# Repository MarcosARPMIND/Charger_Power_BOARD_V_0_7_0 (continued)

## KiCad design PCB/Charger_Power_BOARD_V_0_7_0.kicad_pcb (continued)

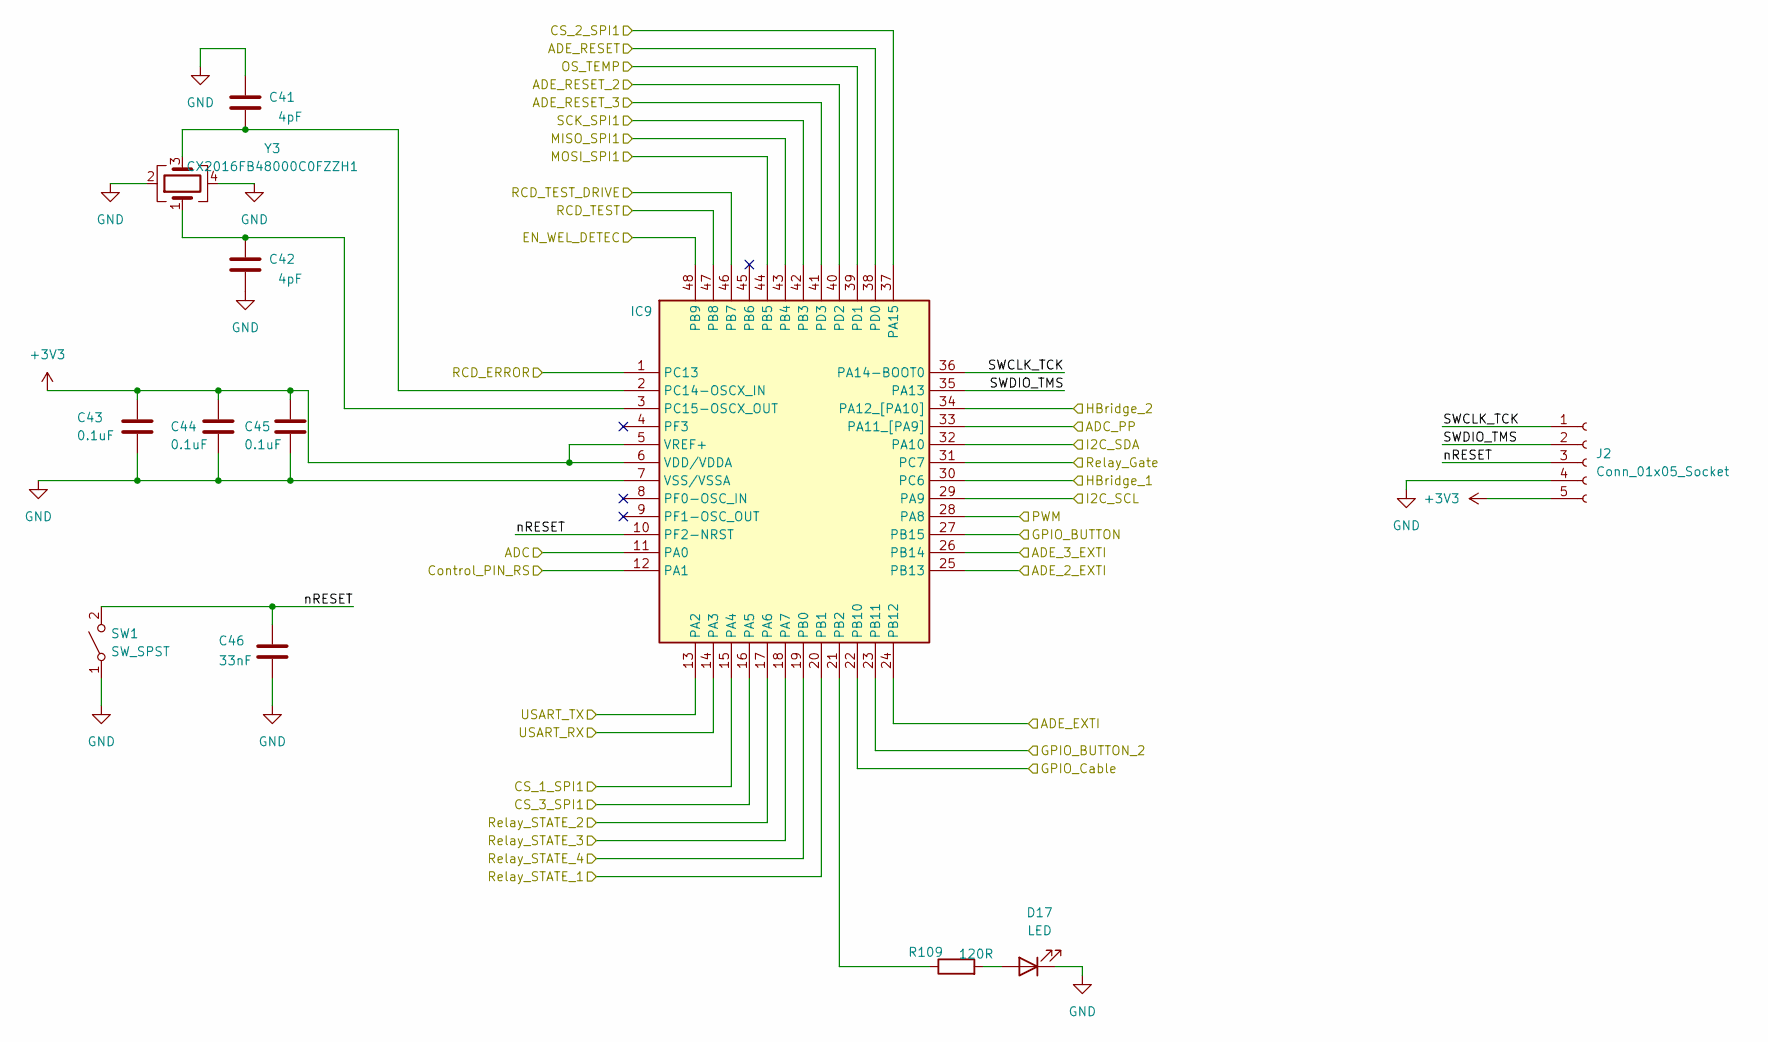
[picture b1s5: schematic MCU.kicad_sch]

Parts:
C41, C42: 4pF; C_0603_1608Metric_Pad1.08x0.95mm_HandSolder; MPN CC0603BRNPO9BN4R0
C43, C44, C45: 0.1uF; C_0603_1608Metric; MPN CL10B104MB8NNNC
C46: 33nF; C_0603_1608Metric_Pad1.08x0.95mm_HandSolder; MPN 0603B333J500CT
D17: LED; LED_0603_1608Metric
IC9: STM32C031C6T6; QFP50P900X900X160-48N; MPN STM32C031C6T6
J2: Conn_01x05_Socket; PinHeader_1x05_P2.54mm_Vertical
R109: 120R; R_0603_1608Metric; MPN RE0603FRE07150RL
SW1: SW_SPST; SW_SPST_B3U-1000P; MPN B3U-1000PM
Y3: CX2016FB48000C0FZZH1; Crystal_SMD_2016-4Pin_2.0x1.6mm; MPN CX2016FB48000C0FZZH1

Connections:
+3V3: C43.1, C44.1, C45.1, IC9.5 (VREF+), IC9.6 (VDD/VDDA), J2.5; also elsewhere on the board
/ADC_PP_resistor: IC9.33 (PA11_[PA9]); also elsewhere on the board
/ADE_RESET: IC9.38 (PD0); also elsewhere on the board
/ADE_RESET_2: IC9.40 (PD2); also elsewhere on the board
/ADE_RESET_3: IC9.41 (PD3); also elsewhere on the board
/CABLE_lock: IC9.22 (PB10); also elsewhere on the board
/Control_Pilot/Pilot_ADC: IC9.11 (PA0); also elsewhere on the board
/Control_Pilot/Pilot_PWM: IC9.28 (PA8); also elsewhere on the board
/EN_WEL_Detec: IC9.48 (PB9); also elsewhere on the board
/GPIO_BUTTON: IC9.27 (PB15); also elsewhere on the board
/GPIO_BUTTON_2: IC9.23 (PB11); also elsewhere on the board
/Gate_Relay: IC9.31 (PC7); also elsewhere on the board
/HBridge_1: IC9.30 (PC6); also elsewhere on the board
/HBridge_2: IC9.34 (PA12_[PA10]); also elsewhere on the board
/I2C_SCL: IC9.29 (PA9); also elsewhere on the board
/I2C_SDA: IC9.32 (PA10); also elsewhere on the board
/IRQ_ADE: IC9.24 (PB12); also elsewhere on the board
/IRQ_ADE_2: IC9.25 (PB13); also elsewhere on the board
/IRQ_ADE_3: IC9.26 (PB14); also elsewhere on the board
/Line_1_Status: IC9.20 (PB1); also elsewhere on the board
/Line_2_Status: IC9.17 (PA6); also elsewhere on the board
/Line_3_Status: IC9.18 (PA7); also elsewhere on the board
/MCU/SWCLK_TCK: IC9.36 (PA14-BOOT0), J2.1
/MCU/SWDIO_TMS: IC9.35 (PA13), J2.2
/MCU/nRESET: C46.2, IC9.10 (PF2-NRST), J2.3, SW1.2 (B)
/Neutral_Line_Status: IC9.19 (PB0); also elsewhere on the board
/OS_TEMP: IC9.39 (PD1); also elsewhere on the board
/RCD_FAULT: IC9.1 (PC13); also elsewhere on the board
/RCD_TEST_DRIVE: IC9.46 (PB7); also elsewhere on the board
/RDC_TEST: IC9.47 (PB8); also elsewhere on the board
/RS_CTRL_PIN: IC9.12 (PA1); also elsewhere on the board
/SPI_CS_1: IC9.15 (PA4); also elsewhere on the board
/SPI_CS_2: IC9.37 (PA15); also elsewhere on the board
/SPI_CS_3: IC9.16 (PA5); also elsewhere on the board
/SPI_MISO: IC9.43 (PB4); also elsewhere on the board
/SPI_MOSI: IC9.44 (PB5); also elsewhere on the board
/SPI_SCK: IC9.42 (PB3); also elsewhere on the board
/UART0_RX: IC9.14 (PA3); also elsewhere on the board
/UART0_TX: IC9.13 (PA2); also elsewhere on the board
GND: C41.2, C42.1, C43.2, C44.2, C45.2, C46.1, D17.1 (K), IC9.7 (VSS/VSSA), J2.4, SW1.1 (A), Y3.2, Y3.4; also elsewhere on the board
unnamed: D17.2 (A), R109.2
unnamed: IC9.21 (PB2), R109.1
unnamed: C41.1, IC9.2 (PC14-OSCX_IN), Y3.3
unnamed: C42.2, IC9.3 (PC15-OSCX_OUT), Y3.1

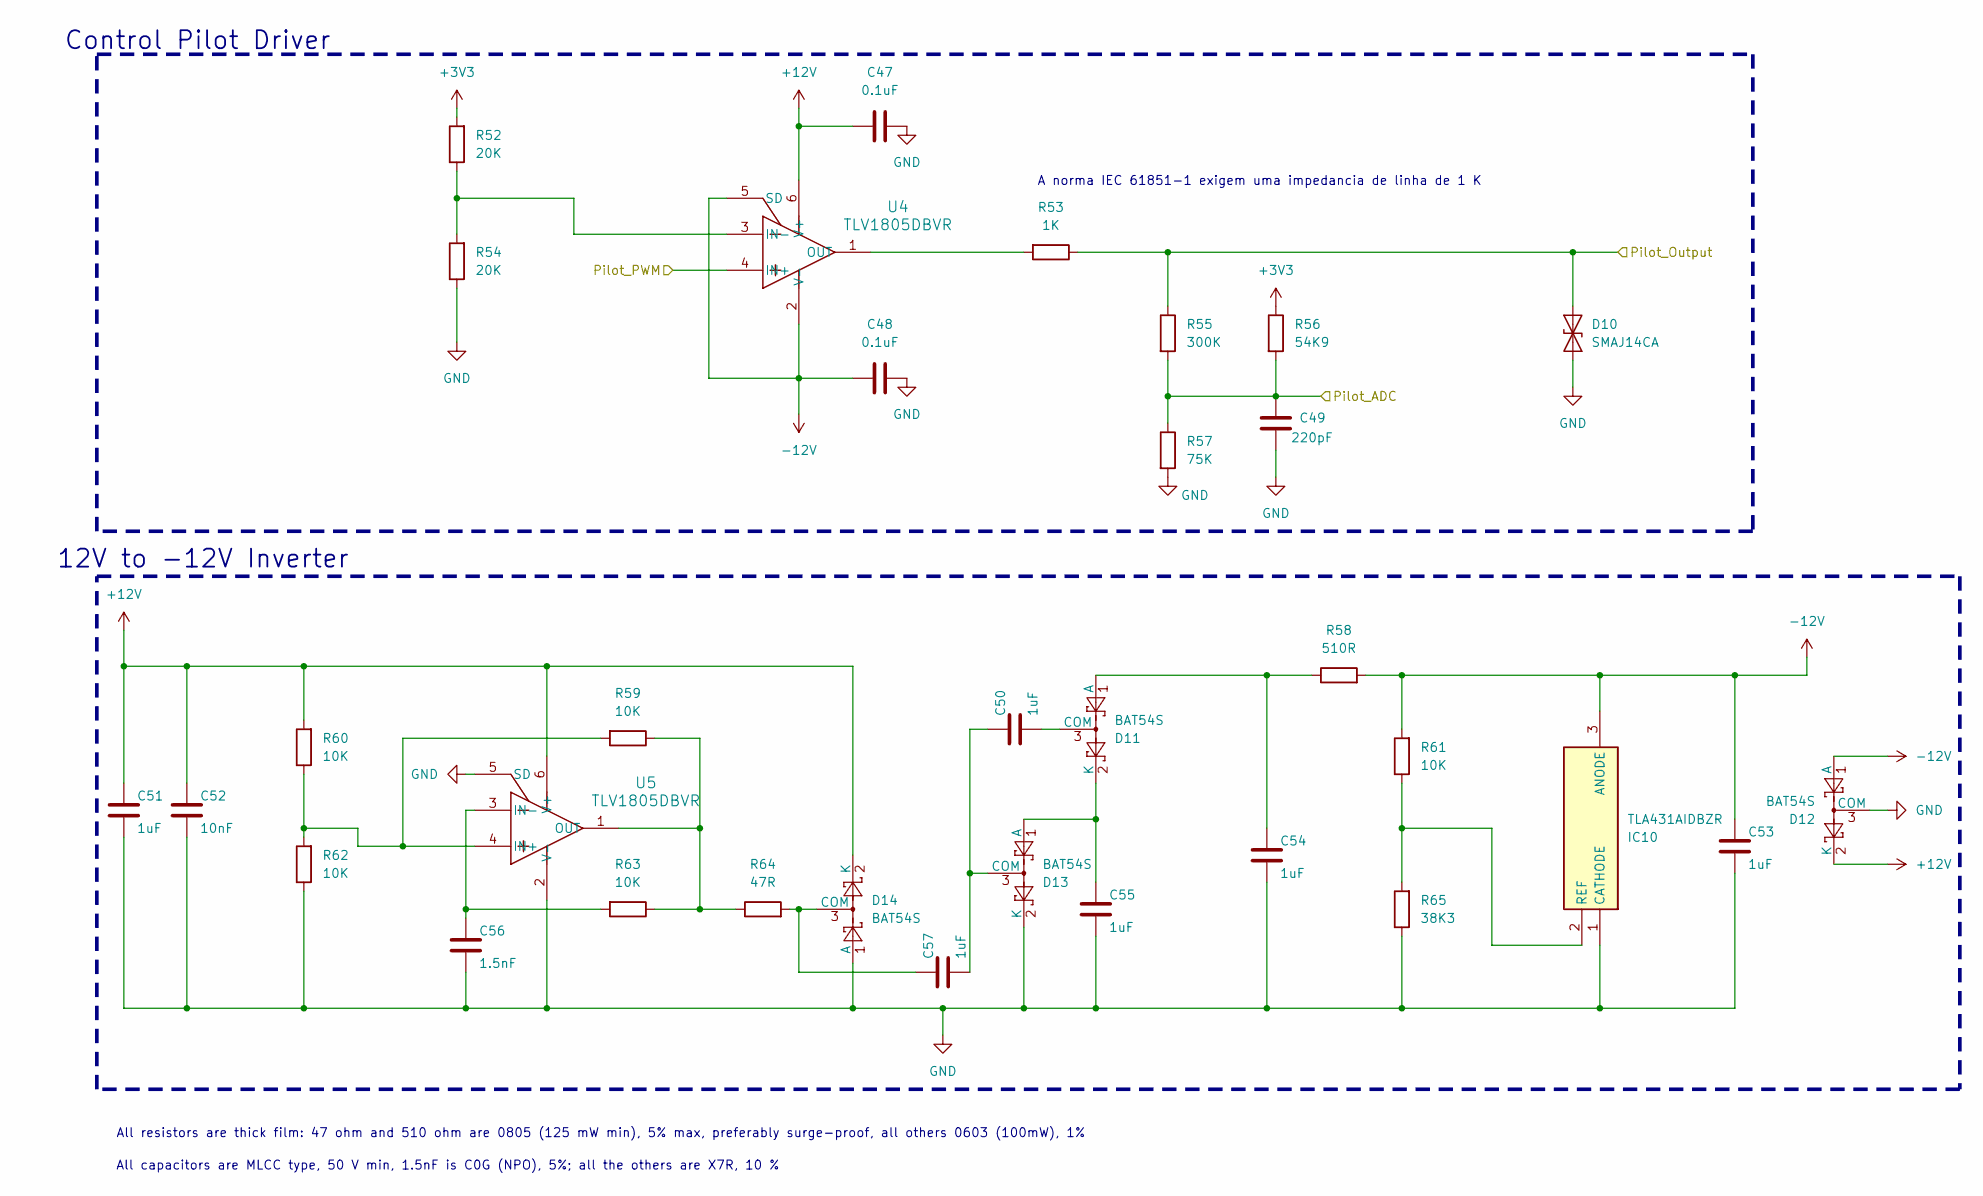
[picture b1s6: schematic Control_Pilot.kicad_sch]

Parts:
C47, C48: 0.1uF; C_0603_1608Metric; MPN CL10B104MB8NNNC
C49: 220pF; C_0603_1608Metric_Pad1.08x0.95mm_HandSolder; MPN CC0603JRX7R9BB221
C50, C51, C53, C54, C55, C57: 1uF; C_0603_1608Metric_Pad1.08x0.95mm_HandSolder; MPN CL10B105KB8NQNC
C52: 10nF; C_0603_1608Metric_Pad1.08x0.95mm_HandSolder; MPN 06035C103MAZ2A
C56: 1.5nF; C_0603_1608Metric_Pad1.08x0.95mm_HandSolder; MPN GCM1885C1H152JA16J
D10: SMAJ14CA; D_SMA; MPN SMAJ14CA-E3/61
D11, D12, D13, D14: BAT54S; SOT-23; MPN BAT54S-7-F
IC10: TLA431AIDBZR; SOT95P237X112-3N
R52, R54: 20K; R_0603_1608Metric; MPN CRCW060320K0FKEC
R53: 1K; R_1206_3216Metric; MPN CMP1206-FX-1001ELF
R55: 300K; R_0603_1608Metric
R56: 54K9; R_0603_1608Metric; MPN CRCW060354K9FKEA
R57: 75K; R_0603_1608Metric; MPN ERJ-PA3F7502V
R58: 510R; R_0805_2012Metric
R59, R60, R61, R62, R63: 10K; R_0603_1608Metric; MPN RCS060310K0FKEA
R64: 47R; R_0805_2012Metric; MPN CRCW080547R0JNEAC
R65: 38K3; R_0603_1608Metric; MPN CRCW060338K3FKEA
U4, U5: TLV1805DBVR; SOT95P280X145-6N; MPN TLV1805DBVR

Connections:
+3V3: R52.2, R56.1; also elsewhere on the board
+12V: C47.1, C51.1, C52.1, D12.2 (K), D14.2 (K), R60.2, U4.6 (V+), U5.6 (V+); also elsewhere on the board
-12V: C48.1, C53.1, D12.1 (A), IC10.3 (ANODE), R58.2, R61.2, U4.2 (V-), U4.5 (SD)
/Control_Pilot/Pilot_ADC: C49.2, R55.2, R56.2, R57.1; also elsewhere on the board
/Control_Pilot/Pilot_PWM: U4.4 (IN+); also elsewhere on the board
/PILOT_OUTPUT_CON: D10.1 (A1), R53.1, R55.1; also elsewhere on the board
GND: C47.2, C48.2, C49.1, C51.2, C52.2, C53.2, C54.2, C55.2, C56.2, D10.2 (A2), D12.3 (COM), D13.2 (K), D14.1 (A), IC10.1 (CATHODE), R54.1, R57.2, R62.1, R65.1, U5.2 (V-), U5.5 (SD); also elsewhere on the board
unnamed: C54.1, D11.1 (A), R58.1
unnamed: C50.2, D11.3 (COM)
unnamed: C55.1, D11.2 (K), D13.1 (A)
unnamed: C50.1, C57.2, D13.3 (COM)
unnamed: C57.1, D14.3 (COM), R64.2
unnamed: IC10.2 (REF), R61.1, R65.2
unnamed: R52.1, R54.2, U4.3 (IN-)
unnamed: R53.2, U4.1 (OUT)
unnamed: R59.2, R60.1, R62.2, U5.4 (IN+)
unnamed: C56.1, R63.2, U5.3 (IN-)
unnamed: R59.1, R63.1, R64.1, U5.1 (OUT)

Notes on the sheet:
A norma IEC 61851-1 exigem uma impedancia de linha de 1 K
All capacitors are MLCC type, 50 V min, 1.5nF is C0G (NPO), 5%; all the others are X7R, 10 %
12V to -12V Inverter
All resistors are thick film: 47 ohm and 510 ohm are 0805 (125 mW min), 5% max, preferably surge-proof, all others 0603 (100mW), 1%
Control Pilot Driver

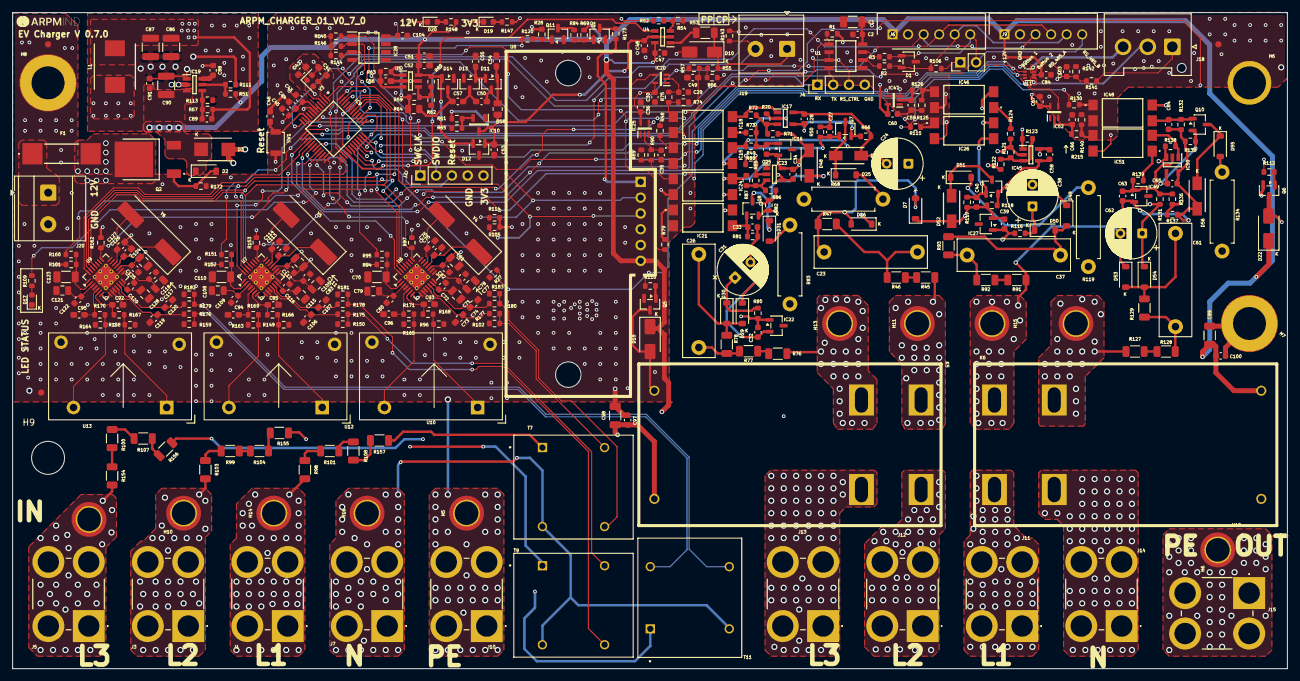
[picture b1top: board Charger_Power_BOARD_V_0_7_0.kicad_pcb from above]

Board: 4 copper layers, 205.0 x 105.5 mm, 365 parts (0 on the bottom side), 210 nets.
